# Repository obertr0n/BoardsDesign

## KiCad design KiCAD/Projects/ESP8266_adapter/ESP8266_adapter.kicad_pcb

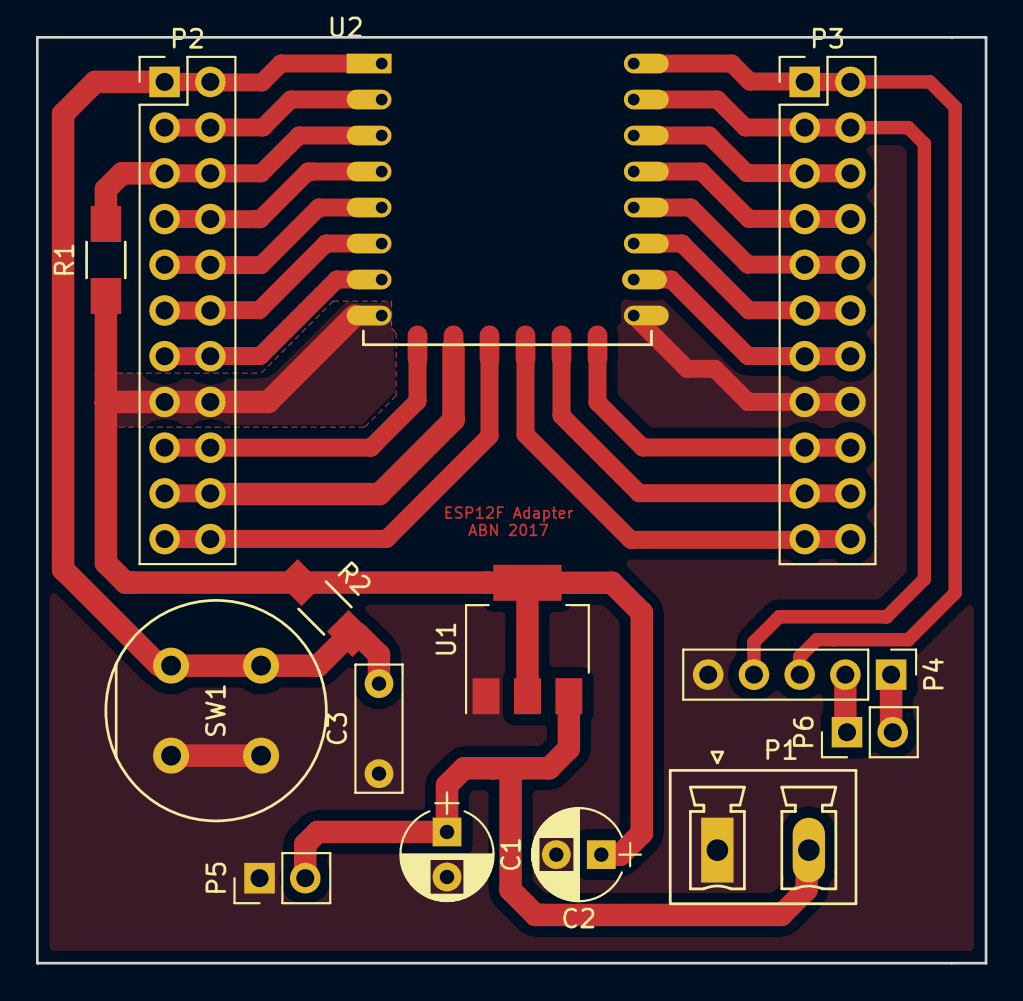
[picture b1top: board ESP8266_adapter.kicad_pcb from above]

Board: 2 copper layers, 52.7 x 51.4 mm, 14 parts (0 on the bottom side), 25 nets.

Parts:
C1: 100uF; CP_Radial_D5.0mm_P2.50mm
C2: 1000uF; CP_Radial_D5.0mm_P2.50mm
C3: 100nF; C_Disc_D7.0mm_W2.5mm_P5.00mm
P1: PWR; PhoenixContact_MCV-G_02x5.08mm_Vertical
P2: CONN_LEFT; Pin_Header_Straight_2x11_Pitch2.54mm
P3: CONN_RIGHT; Pin_Header_Straight_2x11_Pitch2.54mm
P4: UART_PROG; Pin_Header_Straight_1x05_Pitch2.54mm
P5, P6: PWR; Pin_Header_Straight_1x02_Pitch2.54mm
R1, R2: 10k; R_1206_HandSoldering
SW1: RST_SWITCH; Push_E-Switch_KS01Q01
U1: NCP1117DT33G_MountingTab; SOT-223
U2: ESP-12E

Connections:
+3V3: C2.1, P2.15, P2.16, R1.1, R2.1, U1.2, U1.4, U2.8
+5V: C1.1, P1.2, P5.2, U1.3
/3V3: P4.1, P6.2
/5V: P4.2, P6.1
ADC: P2.3, P2.4, U2.2
CS: P2.17, P2.18, U2.17
EN: P2.5, P2.6, R1.2, U2.3
GND: C1.2, C2.2, C3.1, P1.1, P3.15, P3.16, P4.5, P5.1, SW1.2, SW1.4, U1.1, U2.9
GPIO0: P3.9, P3.10, U2.12
GPIO2: P3.11, P3.12, U2.11
GPIO4: P3.7, P3.8, U2.13
GPIO5: P3.5, P3.6, U2.14
GPIO9: P2.21, P2.22, U2.19
GPIO10: P3.21, P3.22, U2.20
GPIO12: P2.11, P2.12, U2.6
GPIO13: P2.13, P2.14, U2.7
GPIO14: P2.9, P2.10, U2.5
GPIO15: P3.13, P3.14, U2.10
GPIO16: P2.7, P2.8, U2.4
MISO: P2.19, P2.20, U2.18
MOSI: P3.19, P3.20, U2.21
RESET: C3.2, P2.1, P2.2, R2.2, SW1.1, SW1.3, U2.1
Rx: P3.3, P3.4, P4.4, U2.15
SCLK: P3.17, P3.18, U2.22
Tx: P3.1, P3.2, P4.3, U2.16

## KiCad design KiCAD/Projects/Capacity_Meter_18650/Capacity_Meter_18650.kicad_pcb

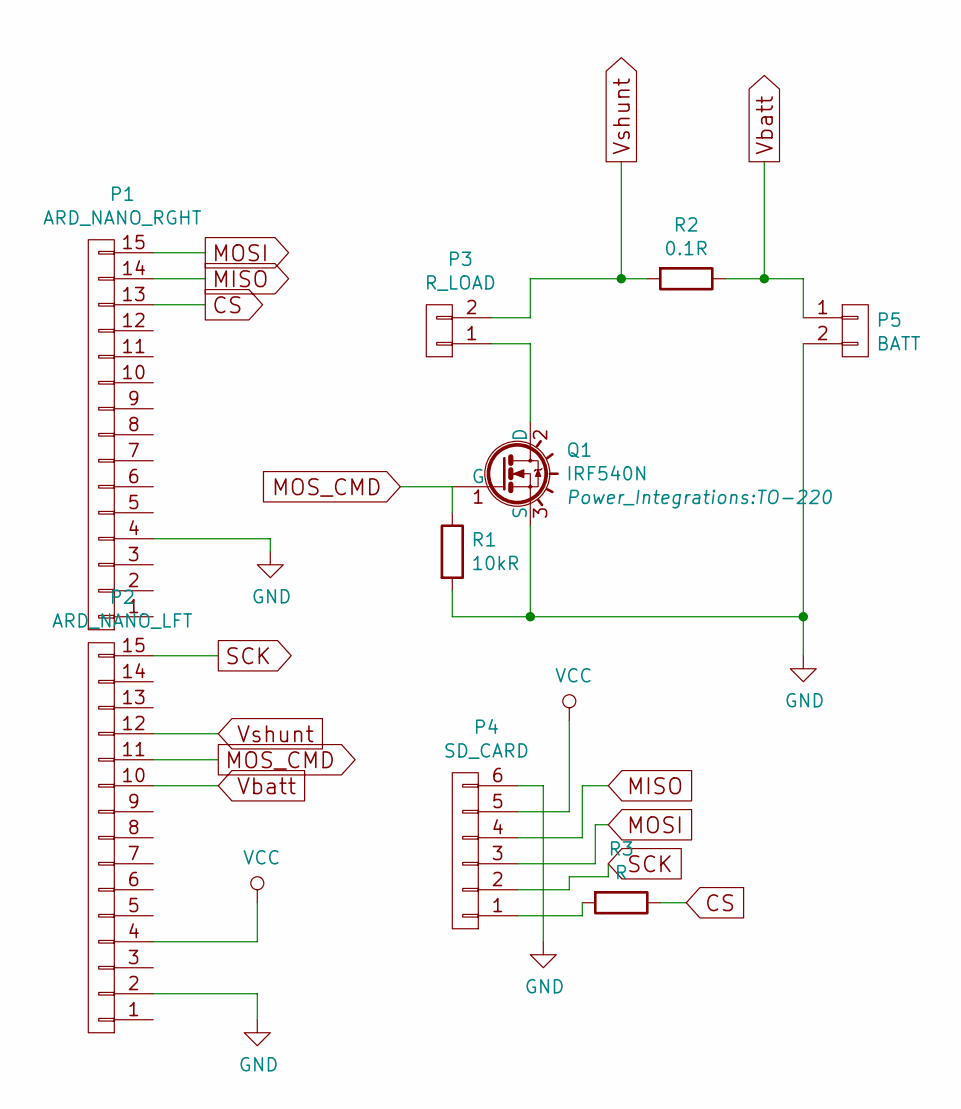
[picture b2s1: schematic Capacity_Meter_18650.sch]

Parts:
P1: ARD_NANO_RGHT; Pin_Header_Straight_1x15_Pitch2.54mm
P2: ARD_NANO_LFT; Pin_Header_Straight_1x15_Pitch2.54mm
P3: R_LOAD; PhoenixContact_MCV-G_02x5.08mm_Vertical
P4: SD_CARD; Pin_Header_Straight_1x06_Pitch2.54mm
P5: BATT; PhoenixContact_MCV-G_02x5.08mm_Vertical
Q1: IRF540N; TO-220
R1: 10kR; Resistor_Horizontal_RM7mm
R2: 0.1R; Resistor_Ceramic_Horizontal_L19mm-W8mm-H8mm-p25mm
R3: R; Resistor_Horizontal_RM7mm

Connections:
CS: P1.13, R3.1
GND: P1.4, P2.2, P4.6, P5.2, Q1.3 (S), R1.2
MISO: P1.14, P4.4
MOSI: P1.15, P4.3
MOS_CMD: P2.11, Q1.1 (G), R1.1
unnamed: P3.1, Q1.2 (D)
unnamed: P4.1, R3.2
SCK: P2.15, P4.2
VCC: P2.4, P4.5
Vbatt: P2.10, P5.1, R2.1
Vshunt: P2.12, P3.2, R2.2

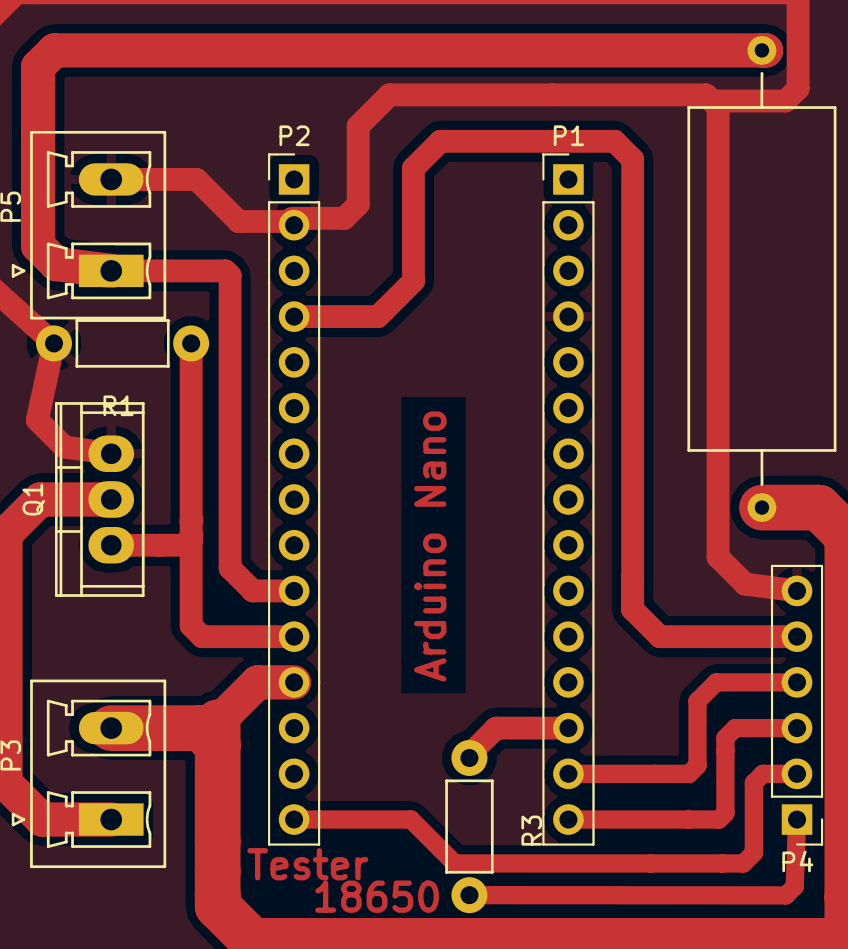
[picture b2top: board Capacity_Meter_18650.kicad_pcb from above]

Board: 2 copper layers, 9 parts (0 on the bottom side), 11 nets.

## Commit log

2017-02-15 Updated the ESP-12F adapter board
2017-02-21 Update with minor modifications
